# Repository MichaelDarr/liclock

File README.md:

# liclock
the libre chess clock

This document is a work in progress!

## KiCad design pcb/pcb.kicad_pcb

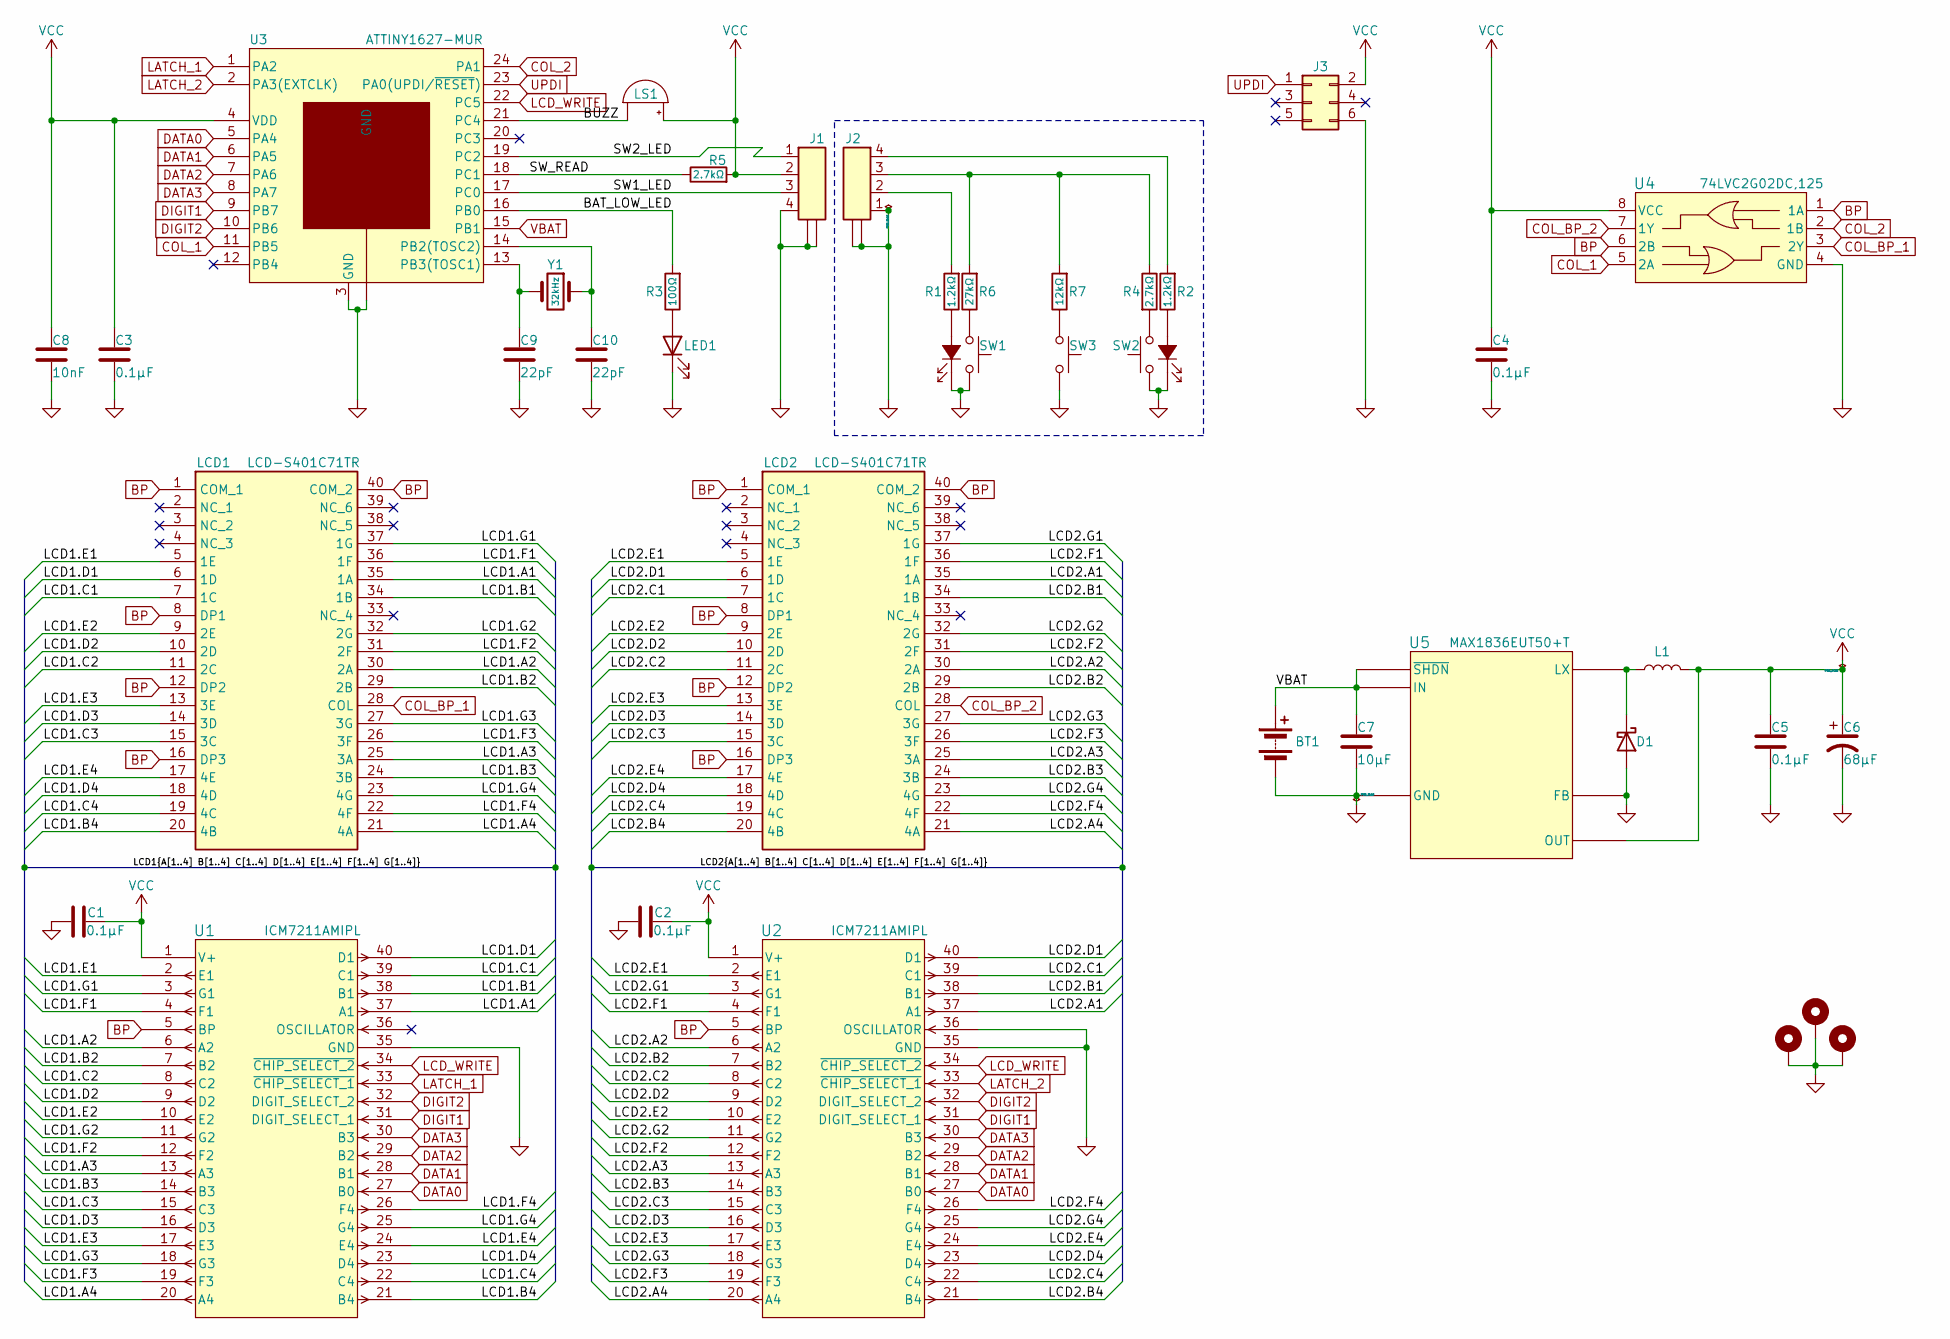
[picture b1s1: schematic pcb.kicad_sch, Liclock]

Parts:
BT1: ~9V; BATTERY
C1, C2, C3, C4, C5: 0.1µF; C_0805_2012Metric_Pad1.18x1.45mm_HandSolder
C6: 68µF; TPSD686K010R0100
C7: 10µF; C_0805_2012Metric_Pad1.18x1.45mm_HandSolder
C8: 10nF; C_0805_2012Metric_Pad1.18x1.45mm_HandSolder
C9, C10: 22pF; C_0805_2012Metric_Pad1.18x1.45mm_HandSolder
D1: Schottky Diode; B240AE-13
H1, H2, H3: MountingHole_Pad; MountingHole_3.5mm_Pad_TopBottom
J1, J2: Conn_01x04; 2005290040; Mouser Part Number 538-200529-0040
J3: UPDI; PinHeader_2x03_P2.54mm_Vertical
L1: 47μH; Inductor_6060
LCD1, LCD2: LCD-S401C71TR
LED1: Red low battery Indicator; 150060RS75000
LS1: Buzzer; CT-1205H-SMT
R1, R2: 1.2kΩ; R_0805_2012Metric_Pad1.20x1.40mm_HandSolder
R3: 100Ω; R_0805_2012Metric_Pad1.20x1.40mm_HandSolder
R4, R5: 2.7kΩ; R_0805_2012Metric_Pad1.20x1.40mm_HandSolder
R6: 27kΩ; R_0805_2012Metric_Pad1.20x1.40mm_HandSolder
R7: 12kΩ; R_0805_2012Metric_Pad1.20x1.40mm_HandSolder
SW1, SW2: MX Grey w/ LED; MX_LED
SW3: 1241.1100.7095; MCS 18 Front
U1, U2: Display Driver; ICM7211AMIPL
U3: MCU; ATTINY1627
U4: NOR, 2 Channels; TC7WZ32FK_LJCT
U5: Voltage Regulator; MAX1836EUT50+T
Y1: 32kHz; CM315D32768HZFT

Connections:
/BAT_LOW_LED: R3.2, U3.16 (PB0)
/BUZZ: LS1.2 (+), U3.21 (PC4)
/LCD1.A1: LCD1.35 (1A), U1.37 (A1)
/LCD1.A2: LCD1.30 (2A), U1.6 (A2)
/LCD1.A3: LCD1.25 (3A), U1.13 (A3)
/LCD1.A4: LCD1.21 (4A), U1.20 (A4)
/LCD1.B1: LCD1.34 (1B), U1.38 (B1)
/LCD1.B2: LCD1.29 (2B), U1.7 (B2)
/LCD1.B3: LCD1.24 (3B), U1.14 (B3)
/LCD1.B4: LCD1.20 (4B), U1.21 (B4)
/LCD1.C1: LCD1.7 (1C), U1.39 (C1)
/LCD1.C2: LCD1.11 (2C), U1.8 (C2)
/LCD1.C3: LCD1.15 (3C), U1.15 (C3)
/LCD1.C4: LCD1.19 (4C), U1.22 (C4)
/LCD1.D1: LCD1.6 (1D), U1.40 (D1)
/LCD1.D2: LCD1.10 (2D), U1.9 (D2)
/LCD1.D3: LCD1.14 (3D), U1.16 (D3)
/LCD1.D4: LCD1.18 (4D), U1.23 (D4)
/LCD1.E1: LCD1.5 (1E), U1.2 (E1)
/LCD1.E2: LCD1.9 (2E), U1.10 (E2)
/LCD1.E3: LCD1.13 (3E), U1.17 (E3)
/LCD1.E4: LCD1.17 (4E), U1.24 (E4)
/LCD1.F1: LCD1.36 (1F), U1.4 (F1)
/LCD1.F2: LCD1.31 (2F), U1.12 (F2)
/LCD1.F3: LCD1.26 (3F), U1.19 (F3)
/LCD1.F4: LCD1.22 (4F), U1.26 (F4)
/LCD1.G1: LCD1.37 (1G), U1.3 (G1)
/LCD1.G2: LCD1.32 (2G), U1.11 (G2)
/LCD1.G3: LCD1.27 (3G), U1.18 (G3)
/LCD1.G4: LCD1.23 (4G), U1.25 (G4)
/LCD2.A1: LCD2.35 (1A), U2.37 (A1)
/LCD2.A2: LCD2.30 (2A), U2.6 (A2)
/LCD2.A3: LCD2.25 (3A), U2.13 (A3)
/LCD2.A4: LCD2.21 (4A), U2.20 (A4)
/LCD2.B1: LCD2.34 (1B), U2.38 (B1)
/LCD2.B2: LCD2.29 (2B), U2.7 (B2)
/LCD2.B3: LCD2.24 (3B), U2.14 (B3)
/LCD2.B4: LCD2.20 (4B), U2.21 (B4)
/LCD2.C1: LCD2.7 (1C), U2.39 (C1)
/LCD2.C2: LCD2.11 (2C), U2.8 (C2)
/LCD2.C3: LCD2.15 (3C), U2.15 (C3)
/LCD2.C4: LCD2.19 (4C), U2.22 (C4)
/LCD2.D1: LCD2.6 (1D), U2.40 (D1)
/LCD2.D2: LCD2.10 (2D), U2.9 (D2)
/LCD2.D3: LCD2.14 (3D), U2.16 (D3)
/LCD2.D4: LCD2.18 (4D), U2.23 (D4)
/LCD2.E1: LCD2.5 (1E), U2.2 (E1)
/LCD2.E2: LCD2.9 (2E), U2.10 (E2)
/LCD2.E3: LCD2.13 (3E), U2.17 (E3)
/LCD2.E4: LCD2.17 (4E), U2.24 (E4)
/LCD2.F1: LCD2.36 (1F), U2.4 (F1)
/LCD2.F2: LCD2.31 (2F), U2.12 (F2)
/LCD2.F3: LCD2.26 (3F), U2.19 (F3)
/LCD2.F4: LCD2.22 (4F), U2.26 (F4)
/LCD2.G1: LCD2.37 (1G), U2.3 (G1)
/LCD2.G2: LCD2.32 (2G), U2.11 (G2)
/LCD2.G3: LCD2.27 (3G), U2.18 (G3)
/LCD2.G4: LCD2.23 (4G), U2.25 (G4)
/SW1_LED: J1.3, U3.17 (PC0)
/SW2_LED: J1.1, U3.19 (PC2)
/SW_READ: R5.1, U3.18 (PC1)
BP: LCD1.1 (COM_1), LCD1.8 (DP1), LCD1.12 (DP2), LCD1.16 (DP3), LCD1.40 (COM_2), LCD2.1 (COM_1), LCD2.8 (DP1), LCD2.12 (DP2), LCD2.16 (DP3), LCD2.40 (COM_2), U1.5 (BP), U2.5 (BP), U4.1 (1A), U4.6 (2B)
COL_1: U3.11 (PB5), U4.5 (2A)
COL_2: U3.24 (PA1), U4.2 (1B)
COL_BP_1: LCD1.28 (COL), U4.3 (2Y)
COL_BP_2: LCD2.28 (COL), U4.7 (1Y)
DATA0: U1.27 (B0), U2.27 (B0), U3.5 (PA4)
DATA1: U1.28 (B1), U2.28 (B1), U3.6 (PA5)
DATA2: U1.29 (B2), U2.29 (B2), U3.7 (PA6)
DATA3: U1.30 (B3), U2.30 (B3), U3.8 (PA7)
DIGIT1: U1.31 (DIGIT_SELECT_1), U2.31 (DIGIT_SELECT_1), U3.9 (PB7)
DIGIT2: U1.32 (DIGIT_SELECT_2), U2.32 (DIGIT_SELECT_2), U3.10 (PB6)
GND: BT1.2 (-), C1.1, C2.1, C3.1, C4.2, C5.2, C6.2, C7.2, C8.2, C9.1, C10.1, D1.2 (A), H1.1, H2.1, H3.1, J1.4, J1.5, J1.6, J3.6, LED1.1 (K), U1.35 (GND), U2.35 (GND), U2.36 (OSCILLATOR), U3.3 (GND), U3.25 (GND), U4.4 (GND), U5.1 (FB), U5.2 (GND)
GND1: J2.1, J2.5, J2.6, SW1.1, SW1.3 (K), SW2.1, SW2.3 (K), SW3.2
LATCH_1: U1.33 (~CHIP_SELECT_1), U3.1 (PA2)
LATCH_2: U2.33 (~CHIP_SELECT_1), U3.2 (PA3(EXTCLK))
LCD_WRITE: U1.34 (~CHIP_SELECT_2), U2.34 (~CHIP_SELECT_2), U3.22 (PC5)
unnamed: D1.1 (K), L1.2, U5.4 (LX)
unnamed: J2.2, R1.2
unnamed: J2.3, R4.1, R6.2, R7.2
unnamed: J2.4, R2.2
unnamed: LED1.2 (A), R3.1
unnamed: R4.2, SW2.2
unnamed: R6.1, SW1.2
unnamed: R7.1, SW3.1
unnamed: R1.1, SW1.4 (A)
unnamed: R2.1, SW2.4 (A)
unnamed: C10.2, U3.14 (PB2(TOSC2)), Y1.1
unnamed: C9.2, U3.13 (PB3(TOSC1)), Y1.2
UPDI: J3.1, U3.23 (PA0(UPDI/~RESET))
VBAT: BT1.1 (+), C7.1, U3.15 (PB1), U5.3 (IN), U5.5 (~SHDN)
VCC: C1.2, C2.2, C3.2, C4.1, C5.1, C6.1, C8.1, J1.2, J3.2, L1.1, LS1.1 (-), R5.2, U1.1 (V+), U2.1 (V+), U3.4 (VDD), U4.8 (VCC), U5.6 (OUT)

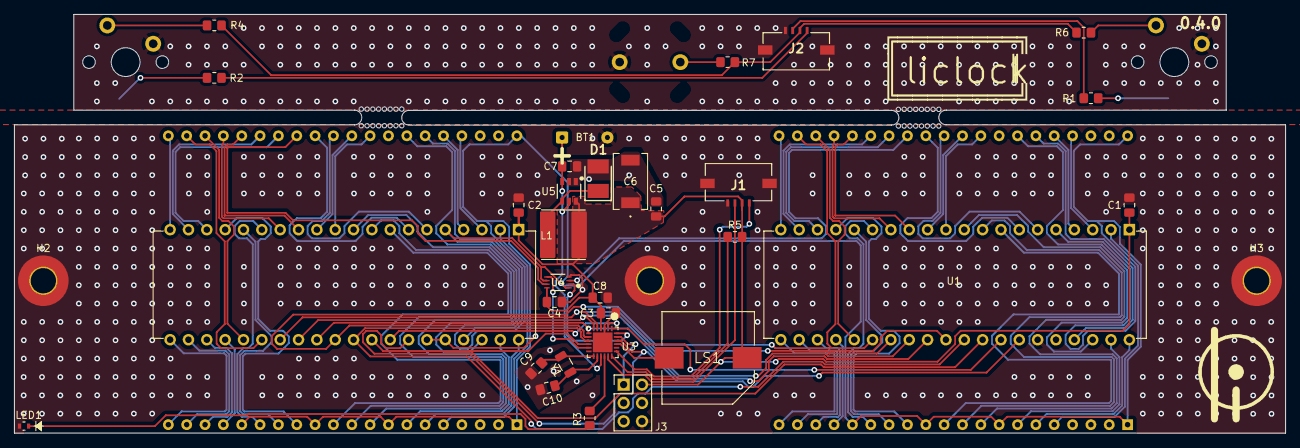
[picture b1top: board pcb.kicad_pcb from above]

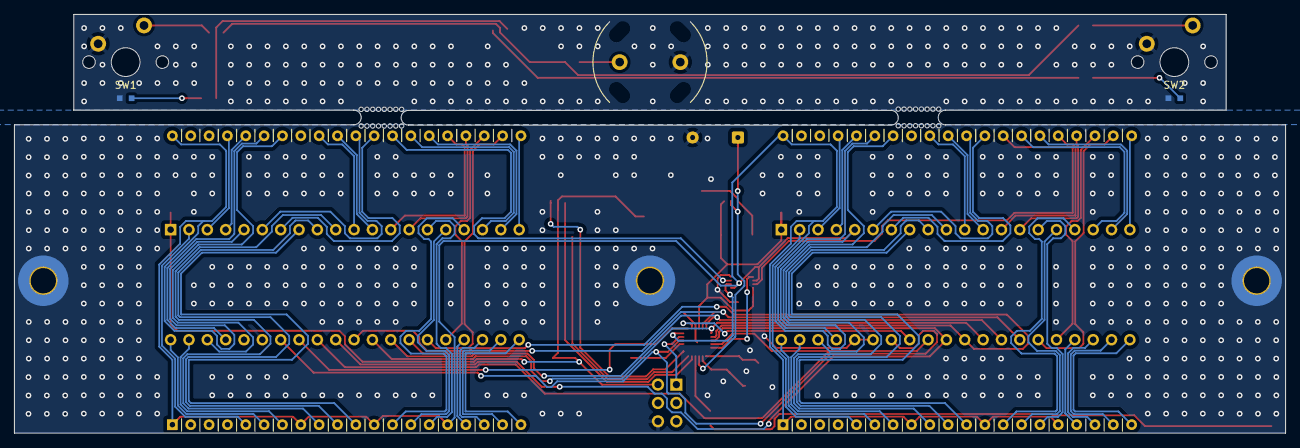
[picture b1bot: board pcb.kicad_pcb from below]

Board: 2 copper layers, 176.0 x 58.0 mm, 39 parts (5 on the bottom side), 92 nets.

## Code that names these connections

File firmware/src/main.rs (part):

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    // Enable timer A
    dp.TCA0.ctrla.write(|w| unsafe { w.bits(0b0000_0001)});

    // Configure PA1..7 as output pins
    dp.PORTA.dirset.write(|w| unsafe {
        w.bits(0b1111_1110)
    });
    // Configure PB0 (low battery led), PB 6..7 (LCD digit selectors) as output pins
    // PB 4..5 were previously enabled here as COL_N pins
    dp.PORTB.dirset.write(|w| unsafe {
        w.bits(0b1100_0001)
    });
    // Configure PC0 (switch 1 led), PC2 (switch 2 led), and PC5 (buzzer) as output pins
    dp.PORTC.dirset.write(|w| unsafe {
        w.bits(0b0001_0101)
    });

    // TODO => set up switch resistor ladder adc pin (PC1/AIN13)
    // dp.PORTC.pin0ctrl.write(|w| unsafe { w.bits(0b0000_1011) });
    // dp.PORTC.pin2ctrl.write(|w| unsafe { w.bits(0b0000_1011) });
    // dp.PORTC.pin4ctrl.write(|w| unsafe { w.bits(0b0000_1011) });
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//         if let Some(ref mut dp) = DP.borrow(cs).borrow_mut().deref_mut() {
//             let ref mut chess_clock = CHESS_CLOCK.borrow(cs).borrow_mut();

//             if dp.PORTC.intflags.read().pc0().bit_is_set() {
//                 // Player A button press detected
//                 dp.PORTC.intflags.modify(|r, w| { w.bits(r.bits() & 0b0000_0001)});
//                 if chess_clock.mode != ClockMode::TurnB {
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//                     }
//                 }
//             }
//             if dp.PORTC.intflags.read().pc2().bit_is_set() {
//                 // Player B button press detected
//                 dp.PORTC.intflags.modify(|r, w| { w.bits(r.bits() & 0b0000_0100)});
//                 if chess_clock.mode != ClockMode::TurnA {
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//                     }
//                 }
//             }
//             if dp.PORTC.intflags.read().pc4().bit_is_set() {
//                 // Control button press detected
//                 dp.PORTC.intflags.modify(|r, w| { w.bits(r.bits() & 0b0001_0000)});
//                 let now = dp.RTC.cnt.read().bits();
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
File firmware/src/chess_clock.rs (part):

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    pub unsafe fn render(&self, player: Player) {
        interrupt::free(|cs| {
            if let Some(ref mut porta) = PORTA.borrow(cs).borrow_mut().deref_mut() {
                // convert PA3 into an output
                porta.ddra.modify(|r, w| w.bits(
                    r.bits() | 0b0000_1000
                ));
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
                            match digit_position {
                                DigitPosition::Second => {
                                    // PA4 low, PA5 low
                                    porta.porta.modify(|r, w| w.bits(
                                        r.bits() & 0b1100_1111
                                    ));
                                },
                                DigitPosition::Decasecond => {
                                    // PA4 high, PA5 low
                                    porta.porta.modify(|r, w| w.bits(
                                        (r.bits() & 0b1101_1111) | 0b0001_0000
                                    ));
                                },
                                DigitPosition::Minute => {
                                    // PA4 low, PA5 high
                                    porta.porta.modify(|r, w| w.bits(
                                        (r.bits() & 0b1110_1111) | 0b0010_0000
                                    ));
                                },
                                DigitPosition::Decaminute => {
                                    // PA4 high, PA5 high
                                    porta.porta.modify(|r, w| w.bits(
                                        r.bits() | 0b0011_0000
                                    ));
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                            }
            
                            if digit & 0b0000_0001 == 1 {
                                // PB2 high
                                portb.portb.modify(|r, w| w.bits(
                                    r.bits() | 0b0000_0100
                                ));
                            } else {
                                // PB2 low
                                portb.portb.modify(|r, w| w.bits(
                                    r.bits() & 0b1111_1011
                                ));
                            }
                            if (digit >> 1) & 0b0000_0001 == 1 {
                                // PA7 high
                                porta.porta.modify(|r, w| w.bits(
                                    r.bits() | 0b1000_0000
                                ));
                            } else {
                                // PA7 low
                                porta.porta.modify(|r, w| w.bits(
                                    r.bits() & 0b0111_1111
                                ));
                            }
                            if (digit >> 2) & 0b0000_0001 == 1 {
                                // PA6 high
                                porta.porta.modify(|r, w| w.bits(
                                    r.bits() | 0b0100_0000
                                ));
                            } else {
                                // PA6 low
                                porta.porta.modify(|r, w| w.bits(
                                    r.bits() & 0b1011_1111
                                ));
                            }
                            if (digit >> 3) & 0b0000_0001 == 1 {
                                // PA3 high
                                porta.porta.modify(|r, w| w.bits(
                                    r.bits() | 0b0000_1000
                                ));
                            } else {
                                // PA3 low
                                porta.porta.modify(|r, w| w.bits(
                                    r.bits() & 0b1111_0111
                                ));
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                        }
                    }
                }
                // revert PA3 back to a pull-up input, driving high for the transition (see datasheet page 61, section 10.1.3)
                // Additionally, pull b high to end the write
                porta.porta.modify(|r, w| w.bits(
                    r.bits() | 0b0000_1100
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
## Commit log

2023-11-22 implement firmware mvp
2023-11-22 Add schematic draft
2023-11-22 Add readme disclaimer
2023-11-27 Implement timer swaps on new clock
2023-11-27 Display increment immediately
2023-12-01 Migrate to attiny84a
2023-12-02 Implement u16 clock representation
2023-12-02 finalize & document mvp
2023-12-04 Implement time adjustment
2023-12-04 persist time changes through set cycles
2023-12-06 Implement configuration persistence
2023-12-09 Update schematic
2023-12-09 add sanity check
2023-12-12 Improve signal integrity
2023-12-15 Simplify switch reading loop
2023-12-15 initialize pcb design
2023-12-22 begin split pcb layout
2023-12-22 Support four clock profiles
2023-12-22 Separate board halves
2023-12-27 Finish basic pcb layout
2023-12-28 solve solder mask errors
2023-12-29 Prepare for connection
2023-12-29 crush every error
2023-12-30 Add some snazy art
2023-12-30 Add mouse bites
2023-12-30 Add some models
2024-01-02 0.1.0
2024-01-02 Add picture of 0.1.0 schematic
2024-01-02 narrow down schematic for v0.2.0
2024-01-02 Fix violations
2024-01-04 standardize cross-connector net names
2024-01-04 0.2.0
2024-01-05 Update mcs 18 front footprint
2024-01-07 remove the self
2024-01-07 omit backups from git
2024-01-07 Remove outdated schematic
2024-01-23 Set up firmware for new board
2024-02-05 Move micro onto LCD board
2024-02-21 Initialize enclosure
2024-02-21 back up pcb work
2024-02-21 Redo pcb layout
2024-02-22 Finalize initial design
2024-02-22 Make clock smaller
2024-02-23 Fix mounting hole margin
2024-02-23 Add extensive mounting holes
2024-02-23 Finalize v3
2024-02-23 compile enclosure
2024-02-23 Housecleaning
2024-02-23 Fix paths
2024-02-23 make fine adjustments
2024-02-29 Slight pcb improvements
2024-02-29 Fix many issues
2024-03-01 Upgrade firmware
2024-03-03 Fix pcb issues
2024-03-13 Fine adjustments
2024-03-13 Add footer holes
2024-03-15 Increase switch pin spacing
2024-03-15 Increase footer bezel
